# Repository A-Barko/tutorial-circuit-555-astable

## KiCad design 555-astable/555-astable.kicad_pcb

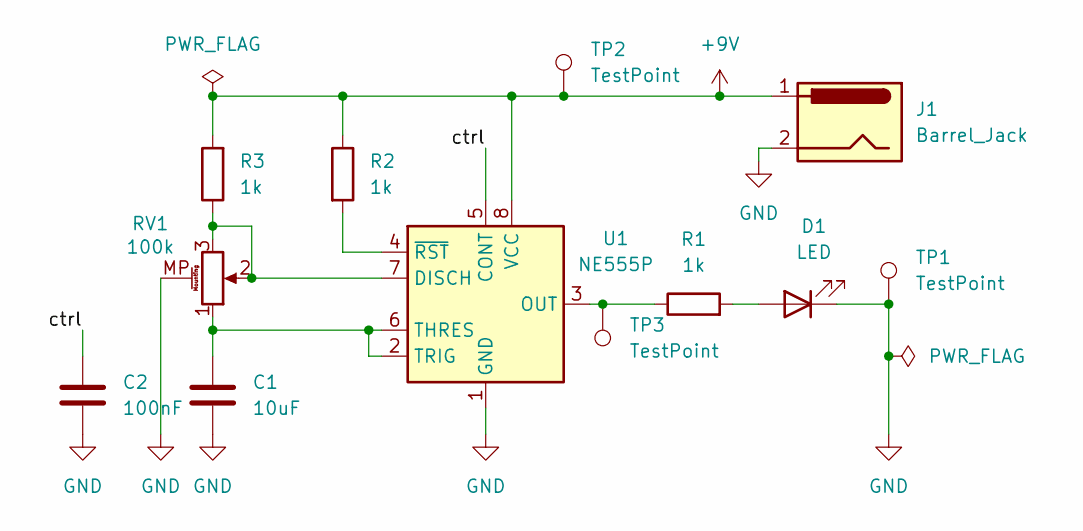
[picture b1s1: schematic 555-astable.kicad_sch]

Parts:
C1: 10uF; CP_Radial_D5.0mm_P2.00mm
C2: 100nF; C_Disc_D5.0mm_W2.5mm_P2.50mm
D1: LED; LED_D3.0mm
J1: Barrel_Jack; BarrelJack_Horizontal
R1, R2, R3: 1k; R_Axial_DIN0207_L6.3mm_D2.5mm_P10.16mm_Horizontal
RV1: 100k; Potentiometer_Bourns_PTV09A-1_Single_Vertical
TP1, TP2, TP3: TestPoint; TestPoint_Plated_Hole_D2.0mm
U1: NE555P; DIP-8_W7.62mm

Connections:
+9V: J1.1, R2.1, R3.2, TP2.1 (1_1), U1.8 (VCC)
/ctrl: C2.1, U1.5 (CONT)
GND: C1.2, C2.2, D1.1 (K), J1.2, RV1.MP (MountPin), TP1.1 (1_1), U1.1 (GND)
unnamed: D1.2 (A), R1.2
unnamed: R3.1, RV1.2, RV1.3, U1.7 (DISCH)
unnamed: R1.1, TP3.1 (1_1), U1.3 (OUT)
unnamed: C1.1, RV1.1, U1.2 (TRIG), U1.6 (THRES)
unnamed: R2.2, U1.4 (~RST)

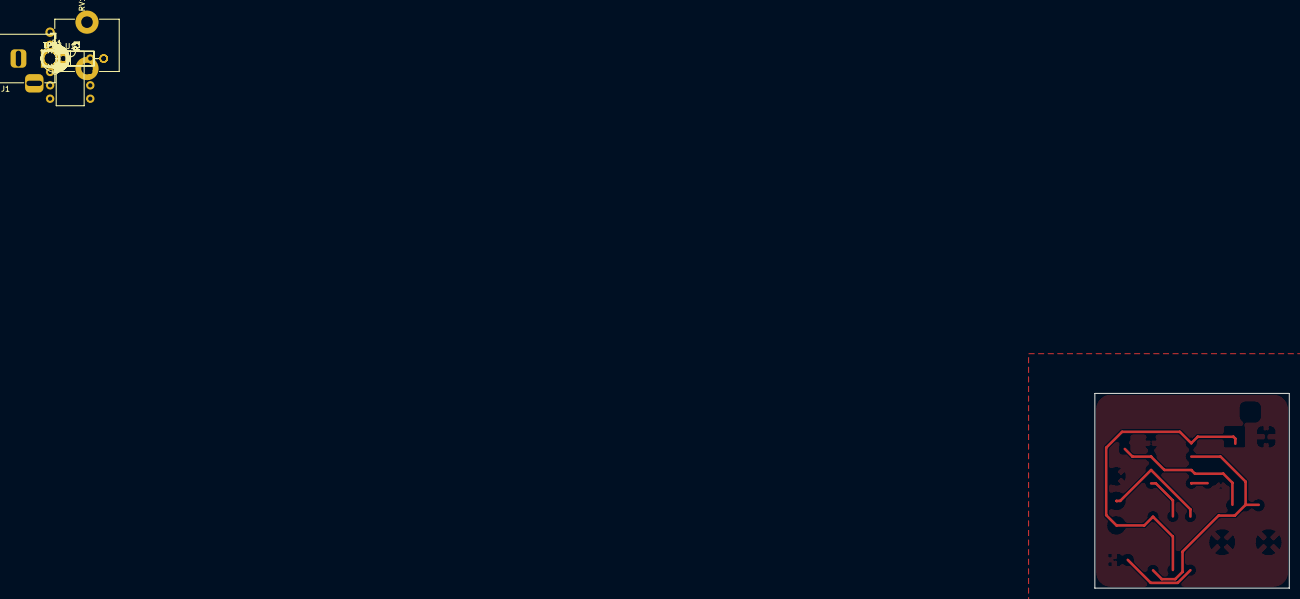
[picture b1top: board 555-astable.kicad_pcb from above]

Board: 2 copper layers, 36.9 x 36.9 mm, 12 parts (0 on the bottom side), 8 nets.
